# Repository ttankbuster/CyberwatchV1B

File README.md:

# CyberwatchV1B
The Cyberwatch is an extensible smartwatch built from scratch, targeting ESP32 hardware. It's current version is V1B.
Cyberwatch runs **Cyan**, a small operating system written in C with an embedded Lua runtime for app handling. Cyan is platform agnostic and can run on the watch and as a native desktop application, so the interface can be developed faster, without hardware in the loop by utilising [Clay](<https://github.com/nicbarker/clay>), a lightweight single header UI layout library. Apps are loaded at runtime from an SD card. 
Clay produces layout commands that are
consumed by either an ST7789V2 display handler on hardware or by SDL on a desktop machine. 
Cyan exposes hardware through a service architecture - a registry of
capabilities that apps and core tabs request as needed and can poll availability of arbitrarily. More info can be found with the [Word doc](<docs\Cyberwatch.docx>).

### Major Features
- Lua App Handling
- Watch-face
- Timer
- Stopwatch
- Remote Shell
- Settings

### Instillation
use `git clone --recurse-submodules https://github.com/ttankbuster/CyberwatchV1B.git` for installation, this git-repo uses submodules.

## Contents

## Functionality
|                                          |                                                                                                                                                                                 |
| ---------------------------------------- | ------------------------------------------------------------------------------------------------------------------------------------------------------------------------------- |
|  | **Watch face** - has digital and analogue variants. The analogue hands are drawn as quads on the same surface primitive used by apps. Shows the time, day of the week and date. |
|           | **Timer** - three spin boxes for hours, minutes and seconds. Button 2 moves between fields, the crown adjusts the value, pressing the crown starts and pauses the timer.        |
|   | **Stopwatch** - same interaction model, counting up rather than down.                                                                                                           |
|        | **App catalogue** - displays a list of apps found on the SD card in rows and launches them.                                                                                     |
|          | **Pong** - a demo app written entirely in Lua, using a bespoke app API.                                                                                                         |
## Hardware
|                                                        | Function                      | Part                                                                                     | Interface    | Notes                                                                                                                                    |
| ------------------------------------------------------ | ------------------------------ | ----------------------------------------------------------------------------------------- | ------------ | ------------------------------------------------------------------------------------------------------------------------------------------ |
|                    | MCU                           | Seeed XIAO ESP32-S3 Plus                                                                 | ---          | 240 MHz dual core, 8 MB PSRAM, 16 MB flash, WiFi + BLE 5.0, 14 µA deep sleep, integrated LiPo charging                                   |
|   | Display                       | 1.69” LCD, ST7789V2                                                                      | SPI          | - 240x280 pixel resolution<br>- 39x31.5mm                                                                                                |
|           | Crown dial                    | MT6701 magnetic encoder + dipole magnet. Annular Belleville popper for tactile feedback. | I2C          |                                                                                                                                          |
|         | GPIO expansion                | MCP23017                                                                                 | I2C          | Frees ESP32 pins for the crown by moving the display RST and BL lines and the buttons onto the expander.                                 |
|                | Storage                       | MicroSD socket                                                                           | SPI          | 10 kΩ pull-ups on CS, MOSI, DAT1, DAT2 and MISO; <br>33 Ω series resistor on VCC to avoid the MCU browning out when the card is inserted |
|                    | Real-time clock & Temperature | DS3231MZ                                                                                 | I2C          | Keeps time across power loss without a WiFi round trip.<br>Source of ambient temperature                                                 |
|          | Battery gauge                 | MAX17048                                                                                 | I2C          |                                                                                                                                          |
|                   | Battery                       | 3.7V 500mAh LiPo                                                                         | ---          | JST-PH Connector                                                                                                                         |
|                | Buttons                       | 3x tactile switch                                                                        | via MCP23017 | Buttons 1 and 2 on the left; button 4 and the crown on the right.                                                                        |

## Software

The software follows a strict naming convention for all source code for the firmware and CyanOS to keep .

| For           | Naming Convention      |
| ------------- | ---------------------- |
| **types**     | `PascalCase`           |
| **fields**    | `camelCase`            |
| **functions** | `snake_case`           |
| **constants** | `SCREAMING_SNAKE_CASE` |

`design/` holds the KiCad schematic and PCB, a FreeCAD case, component datasheets, and BOM spreadsheets for the hardware.

New public symbols should also take a `cyan_*` prefix. Styling is defined in `.clang-format` (stored at root).

Tests live under `test/`:
- `test/test_cyan_shell/` - Unity-style unit test for the shell command parser.
- `test/test_cyan_shell_repl/` - a Python-driven interactive REPL test, run via `pio test -e shell_repl`.

**PlatformIO Environments**

| Environment         | Hardware Target          | Notes                                                                                                                  |
| -------------------- | -------------------------- | -------------------------------------------------------------------------------------------------------------------- |
| `native`             | Windows PC                | uses SDL3 for window handling and rendering; this environment is used for development and iteration without hardware. |
| `esp32c3`            | Seeed XIAO ESP32-C3       | earlier hardware target, watch-face tab only.                                                                        |
| `esp32s3zero`        | ESP32-S3 DevKitM-1        | full hardware target on a generic S3 dev board.                                                                      |
| `xiao_esp32s3_plus`  | Seeed XIAO ESP32-S3 Plus  | full hardware target for the current CyberwatchV1B board.                                                            |
| `shell_repl`         | Windows PC                | dedicated env for interactively testing the shell command parser in isolation, run with `pio test -e shell_repl`.    |

## Getting Started

Clone with submodules:
```
git clone --recurse-submodules https://github.com/ttankbuster/CyberwatchV1B.git
```
The repo vendors its dependencies (Clay, Lua, SDL3 + `_image`/`_ttf`, and two font families) as git submodules rather than package-manager dependencies, so `--recurse-submodules` is required - a plain clone leaves `external/` and the font folders empty.

To build and run the native simulator:
```
pio run -e native
build/native/program.exe
```
The native simulator has currently only been tested on Windows, where it should run out of the box with PlatformIO's toolchain and the SDL3 DLL installer written in python that checks for an instance of the SDL3 DLLs and coppies them into the executable directory if they are not found. This is to speed up starting on another machine. To target real hardware instead, swap `native` for one of the ESP32 environments above, e.g. `pio run -e xiao_esp32s3_plus -t upload`. This will flash to the ESP32-S3-Plus if it is connected with a usb-c cable, then start the operating system and serial monitor.

### Using the simulator

Launching the `native` build opens two windows: the watch display itself, and a separate console window for the interactive shell.

**Native CyanOS controls (`platform/pc/data_pc.c`)**

| Input                      | Maps to                |
| -------------------------- | ---------------------- |
| Keys `1` / `2` / `3` / `4` | Buttons 1 / 2 / 3 / 4  |
| Mouse middle-click         | Button 3               |
| Scroll wheel up/down       | Crown dial up / down   |
| up/down keys               | Crown dial up / down   |

**Shell commands (`cyan/console/cyan_shell.c`)**

| Command                                        | Does                                                                                                            |
| ------------------------------------------------ | ------------------------------------------------------------------------------------------------------------- |
| `help`                                          | Lists all commands                                                                                             |
| `status`                                        | Shows current Cyan status                                                                                      |
| `app list` / `launch <name>` / `exit`           | Manage apps                                                                                                    |
| `app permission add/remove/list <permission>`   | Manage per-app permissions                                                                                     |
| `screenshot`                                    | Saves a PNG of the current display to `screenshots/`, named by the active tab or running app plus a timestamp |
| `settings get/set/list <setting> [value]`       | Read and write settings                                                                                        |

## Apps

Each app is a folder under `apps/` containing a `.cyan_app.lua` manifest plus its Lua script(s). Five example apps ship in the repo: `pong`, `reader`, `RNG`, `sodoku` and `hello_cyan`.

**Manifest fields (`.cyan_app.lua`)**

| Field    | Meaning                                              |
| -------- | -----------------------------------------------------|
| `name`   | Display name shown in the app catalogue              |
| `script` | Entry-point Lua file, relative to the app's folder   |
| `icon`   | Icon bitmap shown in the catalogue                   |
| `dev`    | If `true`, only loaded in debug builds               |

Example (`apps/pong/.cyan_app.lua`):
```lua
return {
    name = "Pong",
    script = "pong.lua",
    icon = "icon.bmp",
    dev = false
}
```

Apps run sandboxed in their own Lua state and only see the API Cyan registers for them:
- `draw.rect(x, y, w, h, [r, g, b, a])` - filled rectangle
- `draw.text(x, y, text, [fontSize, r, g, b])` - text
- `draw.width()` / `draw.height()` - the app's drawable surface sizes
- `Event` - a table of input event constants (`Event.BUTTON1_DOWN`, `Event.SCROLL_UP`, etc.) for use in an app's event-handling code
- `print(...)` - routed into Cyan's own log output, tagged with the app's name

## Architecture

- **Service registry** (`cyan/data/services.h`) - a `ServiceRegistry` of `Service` entries (time, display, input, storage, power, apps, network, bluetooth, notifications, ...), each with `init`/`update`/`shutdown`/`available` functions and a criticality tier. Apps and core tabs can poll services at runtime.
- **Clay-based UI layer** (`cyan/clay_ui.c`) - an immediate-mode layout pass every frame, using [Clay](https://github.com/nicbarker/clay) to produce render commands consumed by a display backend.
- **`Surface` abstraction** (`cyan/data/surface.h`/`.c`) - a per-app pixel buffer that Lua apps draw into via the `draw` API, kept isolated from the OS's own rendering.
- **Platform backend split** - each platform implements its own `display_*` (rendering) and `data_*` (input/event) backends: `platform/pc/` (SDL3) and `platform/esp32/` (ST7789V2 over SPI via Arduino_GFX, MCP23017 I/O expansion).

The MCP23017 must finish initializing before the display's `RST` pulse, and the SD card's SPI setup must run after the display's own SPI init - reversing either hangs the board.

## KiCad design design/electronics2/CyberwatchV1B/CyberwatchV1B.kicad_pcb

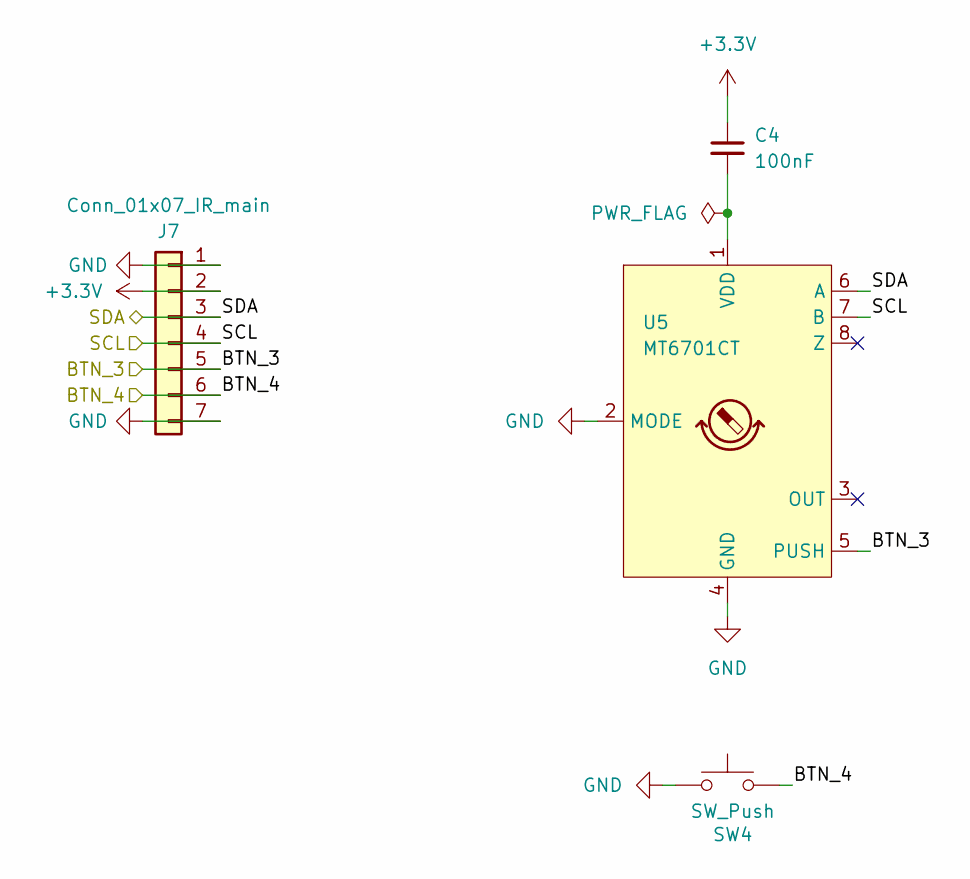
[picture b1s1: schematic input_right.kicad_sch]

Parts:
C4: 100nF; C_0603_1608Metric; MPN CL10B104KB8NNNC
J7: Conn_01x07_IR_main; JST_SH_SM07B-SRSS-TB_1x07-1MP_P1.00mm_Horizontal; MPN SM07B-SRSS-TB(LF)(SN)
SW4: SW_Push; SW_Push_1P1T_NO_CK_KMR2; MPN KMR231NG LFS
U5: MT6701CT; SO-8_3.9x4.9mm_P1.27mm; MPN MT6701CT-STD

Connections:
+3.3V: C4.1, J7.2; also elsewhere on the board
/input_right/BTN_3: J7.5, U5.5 (PUSH); also elsewhere on the board
/input_right/BTN_4: J7.6, SW4.2; also elsewhere on the board
/input_right/SCL: J7.4, U5.7 (B); also elsewhere on the board
/input_right/SDA: J7.3, U5.6 (A); also elsewhere on the board
GND: J7.1, J7.7, SW4.1, U5.2 (MODE), U5.4 (GND); also elsewhere on the board
unnamed: C4.2, U5.1 (VDD)

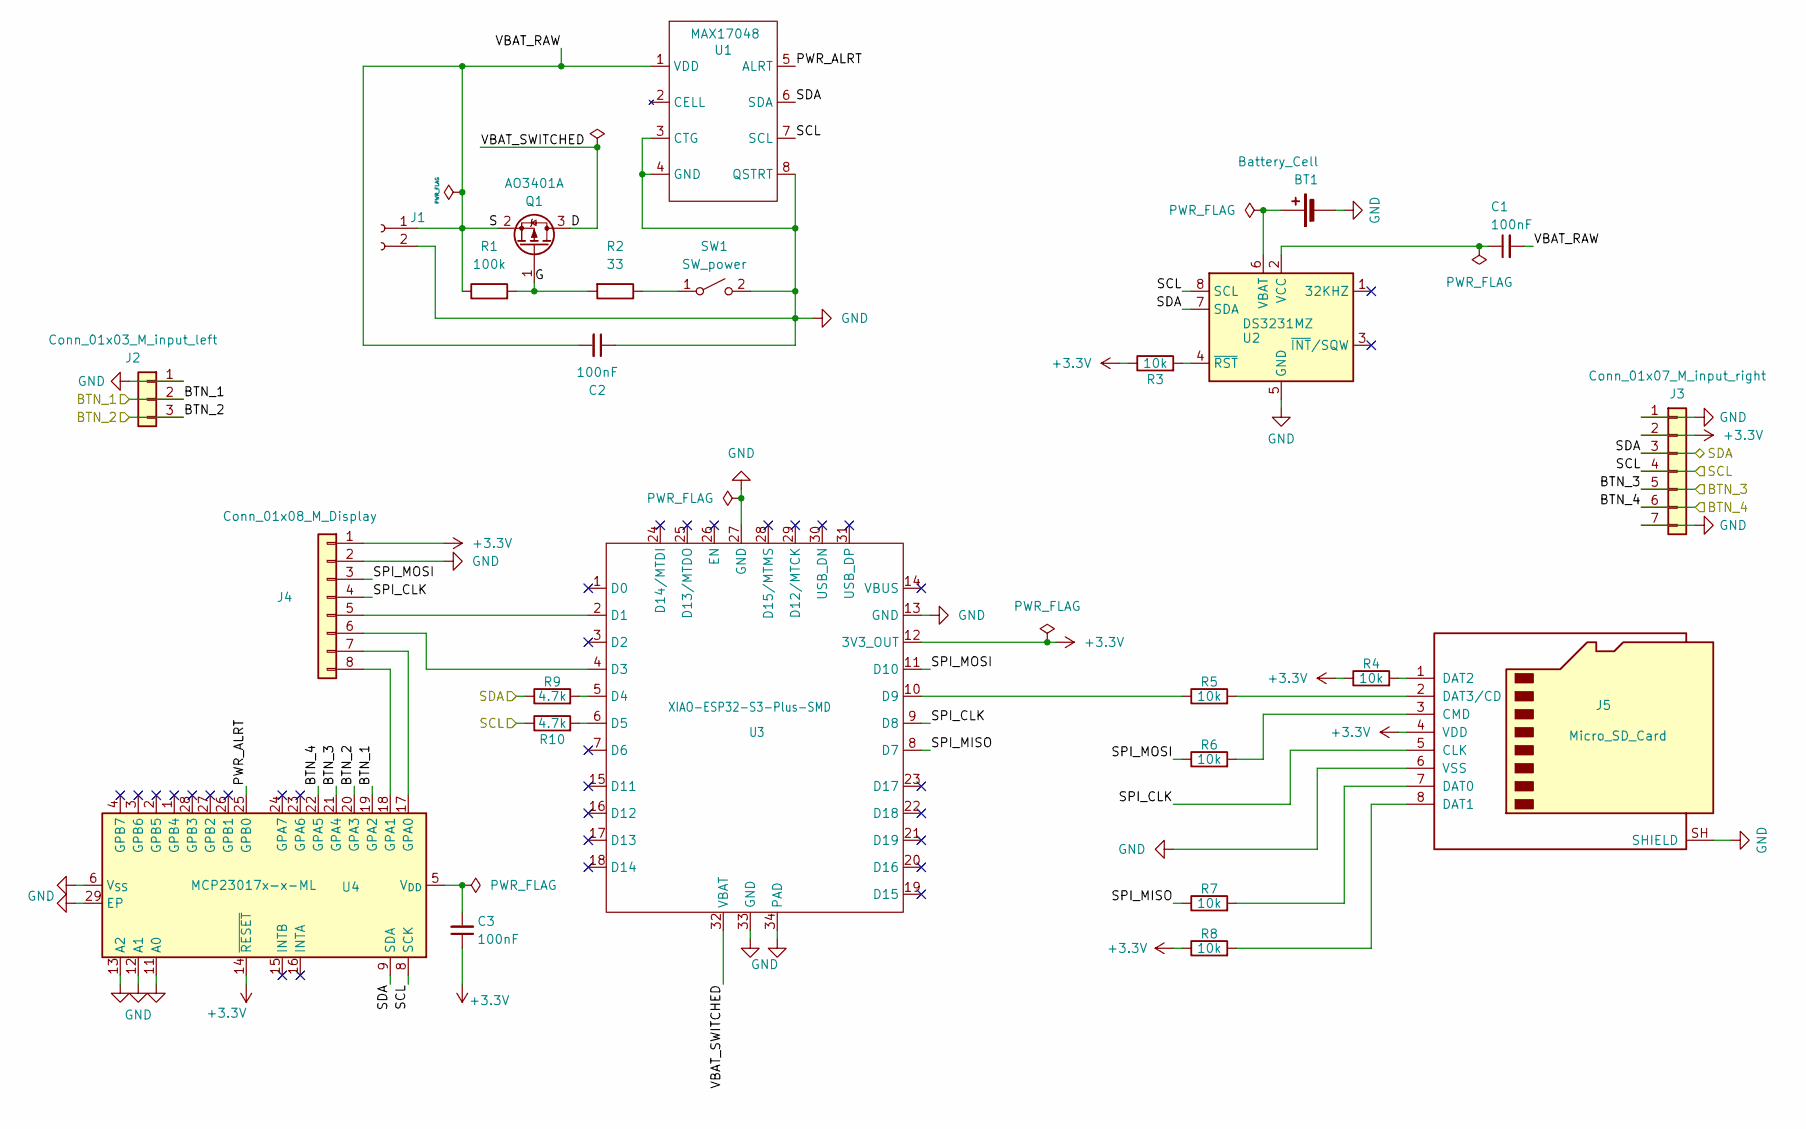
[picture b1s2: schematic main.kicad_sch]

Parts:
BT1: Battery_Cell; BatteryHolder_Keystone_3000_1x12mm; MPN Keystone 3000
C1, C2, C3: 100nF; C_0603_1608Metric; MPN CL10B104KB8NNNC
J1: Conn_01x02_M_Battery; JST_PH_S2B-PH-SM4-TB_1x02-1MP_P2.00mm_Horizontal; MPN S2B-PH-SM4-TB(LF)(SN)
J2: Conn_01x03_M_input_left; JST_SH_SM03B-SRSS-TB_1x03-1MP_P1.00mm_Horizontal; MPN SM03B-SRSS-TB(LF)(SN)
J3: Conn_01x07_M_input_right; JST_SH_SM07B-SRSS-TB_1x07-1MP_P1.00mm_Horizontal; MPN SM07B-SRSS-TB(LF)(SN)
J4: Conn_01x08_M_Display; JST_GH_SM08B-GHS-TB_1x08-1MP_P1.25mm_Horizontal; MPN SM08B-GHS-TB(LF)(SN)
J5: Micro_SD_Card; microSD_HC_Molex_47219-2001; MPN 47219-2001
Q1: AO3401A; SOT-23; MPN AO3401A
R1: 100k; R_0603_1608Metric; MPN RC0603FR-07100KL
R2: 33; R_0603_1608Metric; MPN RC0603FR-0733RL
R3, R4, R5, R6, R7, R8: 10k; R_0603_1608Metric; MPN RC0603FR-0710KL
R9, R10: 4.7k; R_0603_1608Metric; MPN RC0603FR-074K7L
SW1: SW_power; SW_DIP_SPSTx01_Slide_Copal_CHS-01A_W5.08mm_P1.27mm_JPin; MPN CHS-01A
U1: MAX17048; TDFN-8-1EP_2x2mm_P0.5mm_EP0.8x1.2mm; MPN MAX17048G+T10
U2: DS3231MZ; SOIC-8_3.9x4.9mm_P1.27mm; MPN DS3231MZ+
U3: XIAO-ESP32-S3-Plus-SMD
U4: MCP23017x-x-ML; QFN-28-1EP_6x6mm_P0.65mm_EP4.25x4.25mm; MPN MCP23017-E/ML

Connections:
+3.3V: C3.1, J3.2, J4.1 (VCC), J5.4 (VDD), R3.1, R4.1, R8.1, U3.12 (3V3_OUT), U4.14 (~RESET); also elsewhere on the board
/input_right/BTN_3: J3.5, U4.21 (GPA4); also elsewhere on the board
/input_right/BTN_4: J3.6, U4.22 (GPA5); also elsewhere on the board
/input_right/SCL: J3.4, R10.1, U1.7 (SCL), U2.8 (SCL), U4.8 (SCK); also elsewhere on the board
/input_right/SDA: J3.3, R9.1, U1.6 (SDA), U2.7 (SDA), U4.9 (SDA); also elsewhere on the board
/main/BTN_1: J2.2, U4.19 (GPA2); also elsewhere on the board
/main/BTN_2: J2.3, U4.20 (GPA3); also elsewhere on the board
/main/D: Q1.3 (D), U3.32 (VBAT)
/main/G: Q1.1 (G), R1.2, R2.2
/main/PWR_ALRT: U1.5 (ALRT), U4.25 (GPB0)
/main/S: C1.2, C2.2, J1.1, Q1.2 (S), R1.1, U1.1 (VDD)
/main/SPI_CLK: J4.4, J5.5 (CLK), U3.9 (D8)
/main/SPI_MISO: R7.1, U3.8 (D7)
/main/SPI_MOSI: J4.3 (DIN), R6.1, U3.11 (D10)
GND: BT1.2 (-), C2.1, J1.2, J2.1, J3.1, J3.7, J4.2 (GND), J5.6 (VSS), J5.SH (SHIELD), SW1.2 (B), U1.3 (CTG), U1.4 (GND), U1.8 (QSTRT), U2.5 (GND), U3.13 (GND), U3.27 (GND), U3.33 (GND), U3.34 (PAD), U4.6 (V_{SS}), U4.11 (A0), U4.12 (A1), U4.13 (A2), U4.29 (EP); also elsewhere on the board
unnamed: BT1.1 (+), U2.6 (VBAT)
unnamed: J4.5 (CS), U3.2 (D1)
unnamed: J4.6, U3.4 (D3)
unnamed: J4.7, U4.17 (GPA0)
unnamed: J4.8, U4.18 (GPA1)
unnamed: J5.3 (CMD), R6.2
unnamed: J5.7 (DAT0), R7.2
unnamed: J5.8 (DAT1), R8.2
unnamed: J5.1 (DAT2), R4.2
unnamed: J5.2 (DAT3/CD), R5.2
unnamed: R2.1, SW1.1 (A)
unnamed: C1.1, U2.2 (VCC)
unnamed: R3.2, U2.4 (~RST)
unnamed: R9.2, U3.5 (D4)
unnamed: R10.2, U3.6 (D5)
unnamed: R5.1, U3.10 (D9)
unnamed: C3.2, U4.5 (V_{DD})

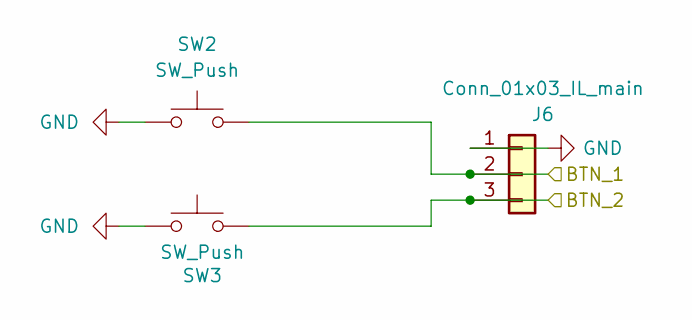
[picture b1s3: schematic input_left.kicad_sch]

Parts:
J6: Conn_01x03_IL_main; JST_SH_SM03B-SRSS-TB_1x03-1MP_P1.00mm_Horizontal; MPN SM03B-SRSS-TB(LF)(SN)
SW2, SW3: SW_Push; SW_Push_1P1T_NO_CK_KMR2; MPN KMR231NG LFS

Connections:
/main/BTN_1: J6.2, SW2.2; also elsewhere on the board
/main/BTN_2: J6.3, SW3.2; also elsewhere on the board
GND: J6.1, SW2.1, SW3.1; also elsewhere on the board

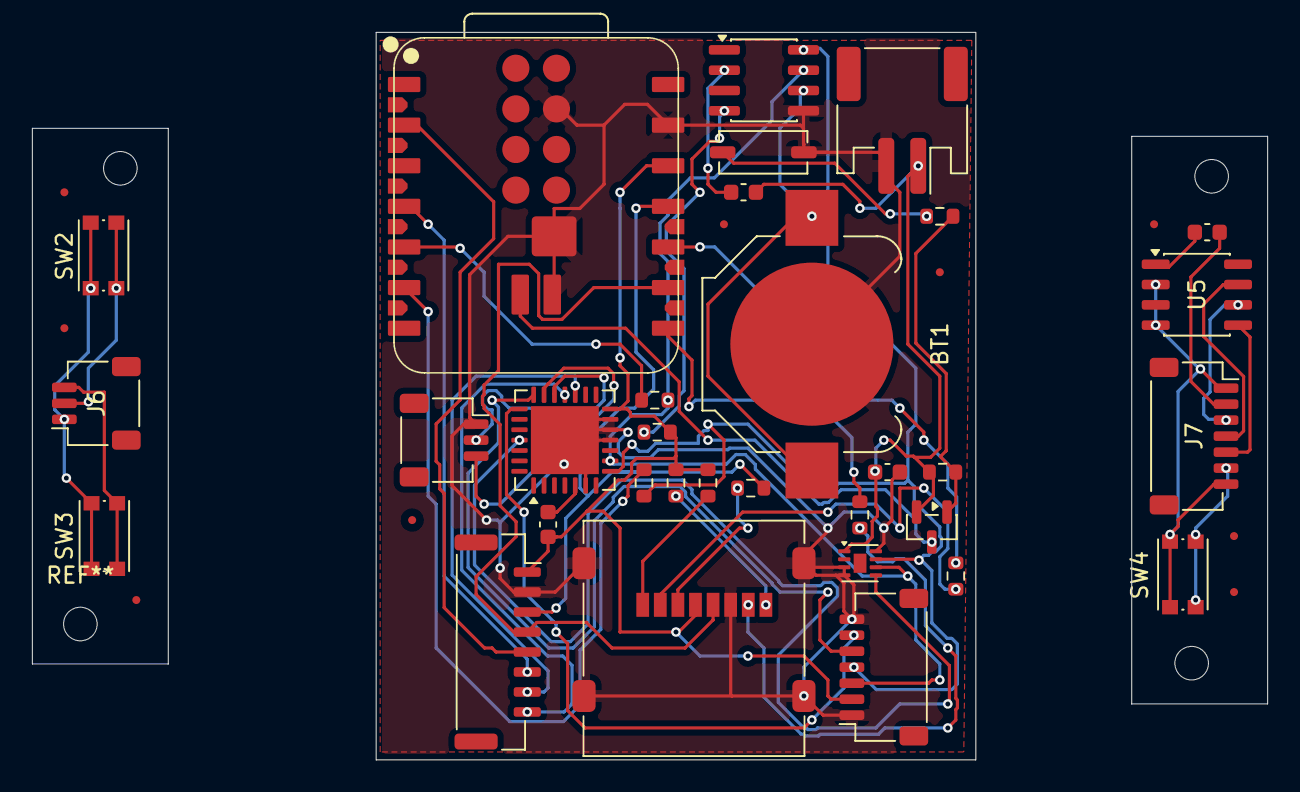
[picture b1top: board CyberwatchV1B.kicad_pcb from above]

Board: 2 copper layers, 77.2 x 45.5 mm, 41 parts (0 on the bottom side), 33 nets.

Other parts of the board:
FID1, FID2, FID3, FID4, FID5, FID6, FID7, FID8, FID9: Fiducial_0.5mm_Mask1.5mm

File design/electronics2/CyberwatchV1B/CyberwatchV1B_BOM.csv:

Reference,Qty,Value,DNP,Exclude from BOM,Exclude from Board,Footprint,Datasheet,MPN
BT1,1,Battery_Cell,,,,Battery:BatteryHolder_Keystone_3000_1x12mm,,Keystone 3000
"C1,C2,C3,C4",4,100nF,,,,Capacitor_SMD:C_0603_1608Metric,,CL10B104KB8NNNC
J1,1,Conn_01x02_M_Battery,,,,Connector_JST:JST_PH_S2B-PH-SM4-TB_1x02-1MP_P2.00mm_Horizontal,,S2B-PH-SM4-TB(LF)(SN)
J2,1,Conn_01x03_M_input_left,,,,Connector_JST:JST_SH_SM03B-SRSS-TB_1x03-1MP_P1.00mm_Horizontal,,SM03B-SRSS-TB(LF)(SN)
J3,1,Conn_01x07_M_input_right,,,,Connector_JST:JST_SH_SM07B-SRSS-TB_1x07-1MP_P1.00mm_Horizontal,,SM07B-SRSS-TB(LF)(SN)
J4,1,Conn_01x08_M_Display,,,,Connector_JST:JST_GH_SM08B-GHS-TB_1x08-1MP_P1.25mm_Horizontal,,SM08B-GHS-TB(LF)(SN)
J5,1,Micro_SD_Card,,,,Connector_Card:microSD_HC_Molex_47219-2001,https://www.we-online.com/components/products/datasheet/6930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,47219-2001
J6,1,Conn_01x03_IL_main,,,,Connector_JST:JST_SH_SM03B-SRSS-TB_1x03-1MP_P1.00mm_Horizontal,,SM03B-SRSS-TB(LF)(SN)
J7,1,Conn_01x07_IR_main,,,,Connector_JST:JST_SH_SM07B-SRSS-TB_1x07-1MP_P1.00mm_Horizontal,,SM07B-SRSS-TB(LF)(SN)
Q1,1,AO3401A,,,,Package_TO_SOT_SMD:SOT-23,http://www.aosmd.com/pdfs/datasheet/AO3401A.pdf,AO3401A
R1,1,100k,,,,Resistor_SMD:R_0603_1608Metric,,RC0603FR-07100KL
R2,1,33,,,,Resistor_SMD:R_0603_1608Metric,,RC0603FR-0733RL
"R3,R4,R5,R6,R7,R8",6,10k,,,,Resistor_SMD:R_0603_1608Metric,,RC0603FR-0710KL
"R9,R10",2,4.7k,,,,Resistor_SMD:R_0603_1608Metric,,RC0603FR-074K7L
SW1,1,SW_power,,,,Button_Switch_SMD:SW_DIP_SPSTx01_Slide_Copal_CHS-01A_W5.08mm_P1.27mm_JPin,,CHS-01A
"SW2,SW3,SW4",3,SW_Push,,,,Button_Switch_SMD:SW_Push_1P1T_NO_CK_KMR2,,KMR231NG LFS
U1,1,MAX17048,,,,Package_DFN_QFN:TDFN-8-1EP_2x2mm_P0.5mm_EP0.8x1.2mm,https://www.analog.com/media/en/technical-documentation/data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,MAX17048G+T10
U2,1,DS3231MZ,,,,Package_SO:SOIC-8_3.9x4.9mm_P1.27mm,http://datasheets.maximintegrated.com/en/ds/DS3231M.pdf,DS3231MZ+
U3,1,XIAO-ESP32-S3-Plus-SMD,,,,Seeed_Studio_XIAO_Series:XIAO-ESP32-S3-Plus-SMD,https://www.mouser.co.uk/datasheet/3/1361/1/esp32_s3_datasheet.pdf,SEEED-113991114
U4,1,MCP23017x-x-ML,,,,Package_DFN_QFN:QFN-28-1EP_6x6mm_P0.65mm_EP4.25x4.25mm,https://ww1.microchip.com/downloads/aemDocuments/documents/A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,MCP23017-E/ML
U5,1,MT6701CT,,,,Package_SO:SO-8_3.9x4.9mm_P1.27mm,https://www.scribd.com/document/932265028/MT6701-Rev-1-8,MT6701CT-STD
